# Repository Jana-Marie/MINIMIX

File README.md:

# MINIMIX

Since my audio setup is running out of inputs, and especially since I usually only need to change my main volume I created the MINIMIX, a minimal 2x4 or 1x8 audio mixer.

## License

Copyright Jana Marie Hemsing 2023. This source describes Open Hardware and is licensed under the CERN- OHL-S v2.

You may redistribute and modify this source and make products using it under the terms of the CERN-OHL-S v2 (LICENSE).

This source is distributed WITHOUT ANY EXPRESS OR IMPLIED WARRANTY, INCLUDING OF MERCHANTABILITY, SATISFACTORY QUALITY AND FITNESS FOR A PARTICULAR PURPOSE. Please see the CERN-OHL-S v2 for applicable conditions.

Source location: https://github.com/Jana-Marie/MINIMIX/ As per CERN-OHL-S v2 section 4, should You produce hardware based on this source, You must where practicable maintain the Source Location visible on the external case of MINIMIX or other products you make using this source

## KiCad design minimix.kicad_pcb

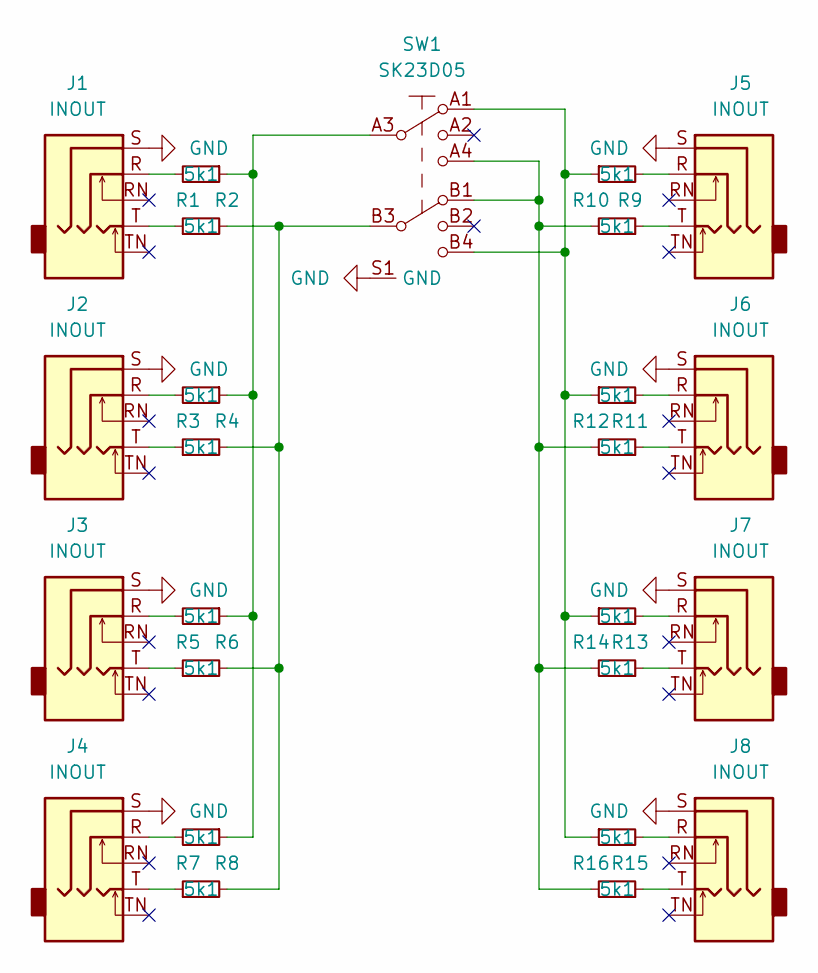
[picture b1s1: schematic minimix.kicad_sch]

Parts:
J1, J2, J3, J4, J5, J6, J7, J8: INOUT; PJ-3126-5A
R1, R2, R3, R4, R5, R6, R7, R8, R9, R10, R11, R12, R13, R14, R15, R16: 5k1; R_0402
SW1: SK23D05

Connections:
GND: J1.S, J2.S, J3.S, J4.S, J5.S, J6.S, J7.S, J8.S, SW1.S1 (GND)
unnamed: J1.R, R1.2
unnamed: J1.T, R2.1
unnamed: J2.R, R3.2
unnamed: J2.T, R4.1
unnamed: J3.R, R5.2
unnamed: J3.T, R6.1
unnamed: J4.R, R7.2
unnamed: J4.T, R8.1
unnamed: J5.R, R9.2
unnamed: J5.T, R10.1
unnamed: J6.R, R11.2
unnamed: J6.T, R12.1
unnamed: J7.R, R13.2
unnamed: J7.T, R14.1
unnamed: R1.1, R3.1, R5.1, R7.1, SW1.A3
unnamed: R2.2, R4.2, R6.2, R8.2, SW1.B3
unnamed: J8.R, R15.2
unnamed: J8.T, R16.1
unnamed: R9.1, R11.1, R13.1, R15.1, SW1.A1, SW1.B4
unnamed: R10.2, R12.2, R14.2, R16.2, SW1.A4, SW1.B1

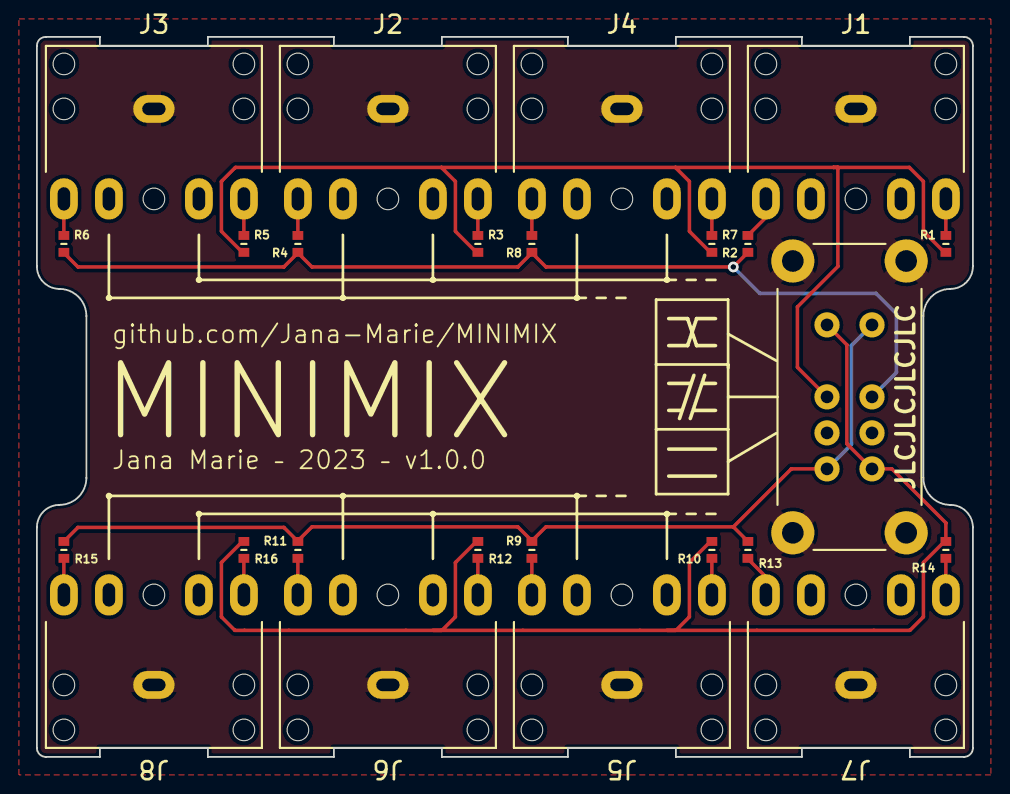
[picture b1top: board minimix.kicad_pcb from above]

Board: 2 copper layers, 52.0 x 40.0 mm, 25 parts (0 on the bottom side), 21 nets.

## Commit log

2023-03-21 added gitignore
2023-03-21 added kicad files
2023-03-21 added pdf
2023-03-21 added image
2023-03-26 fixed typo
